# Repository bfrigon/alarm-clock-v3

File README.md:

alarm-clock (V3)
================

Project page [here][link-project]

Specs
-----

- Arduino based design using the ATMEGA2560 MCU.
- Plays MP3/WAV files from a SD card.
- WiFi connectivity (802.11 b/g/n)
- Automatic clock synchronization using NTP
- Send alarm state to Home Assistant via MQTT
- Large RGB seven segment display
- 16x2 character LCD display
- Night lamp
- Touch keypad
- 24h battery backup

---------------------------------------------------

Home Assistant
--------------
The clock can send the alarm switch state and next alarm timestamp to Home Assistant via MQTT. This allows to run home automations based on the alarm time. It also sends other data such as WiFi signal strength, power state, battery voltage and remaining capacity.

[link-project]:https://www.frigon.info/posts/projects/alarm-clock-v3/

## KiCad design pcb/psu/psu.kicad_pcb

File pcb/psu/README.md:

### Bill of material ###

```
Date    : None
Doc. ID : CLKV3-SCH-07
Project : Alarm Clock (V3)
Title   : Power Supply

Part #  : CLKV3-PC-07
REV.    : A

Components : 40
```

------------------------------------------------------------------------------------------------------------------------

| Qty | Ref.             | Description                                      | Value    | Part #           | Footprint               |
|-----|------------------|--------------------------------------------------|----------|------------------|-------------------------|
| 1   | J3               | Header - Single Row - 2 Pos                      | BATTERY  | S2B-PH-K-S       | conn-jst:S2B-PH-K       |
| 1   | J1               | Header - Dual Row - 6 Pos                        | VIN      | TSW-103-07-F-D   | conn-header:HDR-M-2x03  |
| 1   | J2               | Header - Single Row - 4 Pos                      | SIGNAL   | TSW-104-07-F-S   | conn-header:HDR-M-1x04  |
| 2   | Q1-Q2            | 40V NPN small signal transistor                  | MMST3904 | -                | smt-sot:SOT23           |
| 1   | U2               | Li-Ion Battery charger and Power-Path management | -        | BQ24075          | smt-qfn:QFN16-EP-3x3    |
| 1   | U1               | System-side Impedance Track Fuel Gauge           | -        | BQ27441-G1       | smt-son:PDSO-N12        |
| 1   | U3               | 2V to 16V Buck-Boost converter                   | -        | TPS630701        | smt-qfn:VQFN15N         |
| 1   | R2               | Resistor                                         | 0.01 1%  | -                | smt:R-1206              |
| 1   | R10              | Resistor                                         | 0        | -                | smt:R-0603              |
| 1   | R9               | Resistor                                         | 1.1k     | -                | smt:R-0603              |
| 5   | R3-R6, R12       | Resistor                                         | 100k     | -                | smt:R-0603              |
| 1   | C4               | Capacitor                                        | 100nF    | -                | smt:C-0603              |
| 6   | R1, R11, R13-R16 | Resistor                                         | 10k      | -                | smt:R-0603              |
| 2   | C3, C5           | Capacitor                                        | 10uF     | -                | smt:C-0603              |
| 5   | C1-C2, C11-C13   | Capacitor                                        | 10uF     | -                | smt:C-0805              |
| 1   | C10              | Capacitor                                        | 1uF      | -                | smt:C-0603              |
| 3   | C6-C8            | Capacitor                                        | 22uF     | -                | smt:C-0805              |
| 1   | C9               | Capacitor                                        | 470nF    | -                | smt:C-0603              |
| 1   | R8               | Resistor                                         | 5.6k     | -                | smt:R-0603              |
| 1   | R17              | Resistor                                         | 680      | -                | smt:R-0603              |
| 1   | R7               | Resistor                                         | 787k     | -                | smt:R-0603              |
| 1   | D1               | Led                                              | RED      | 150080RS75000    | smt:LED-0805            |
| 1   | L1               | Inductor                                         | 1.5uH    | SPM5030T-1R5M-HZ | smt-inductor:SPM5030-HZ |

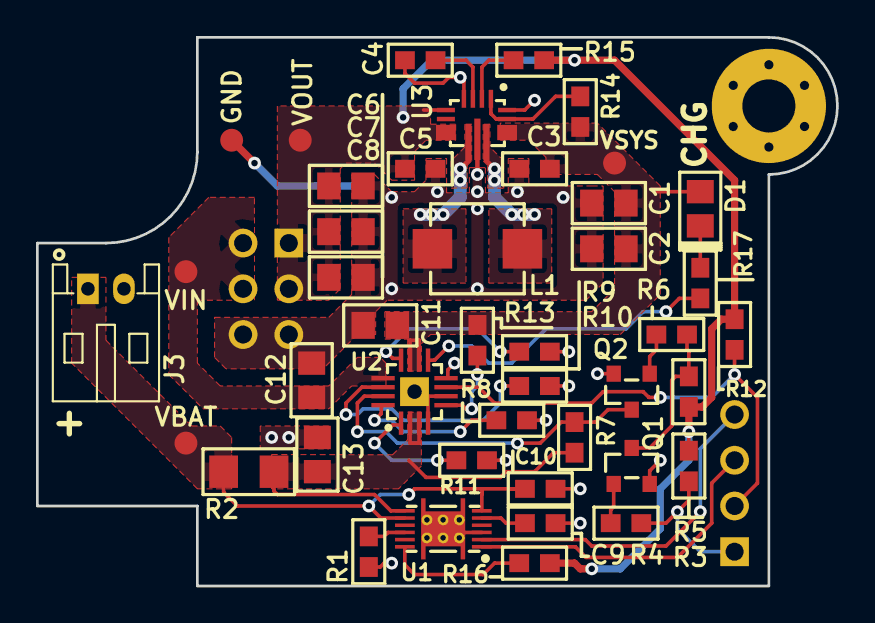
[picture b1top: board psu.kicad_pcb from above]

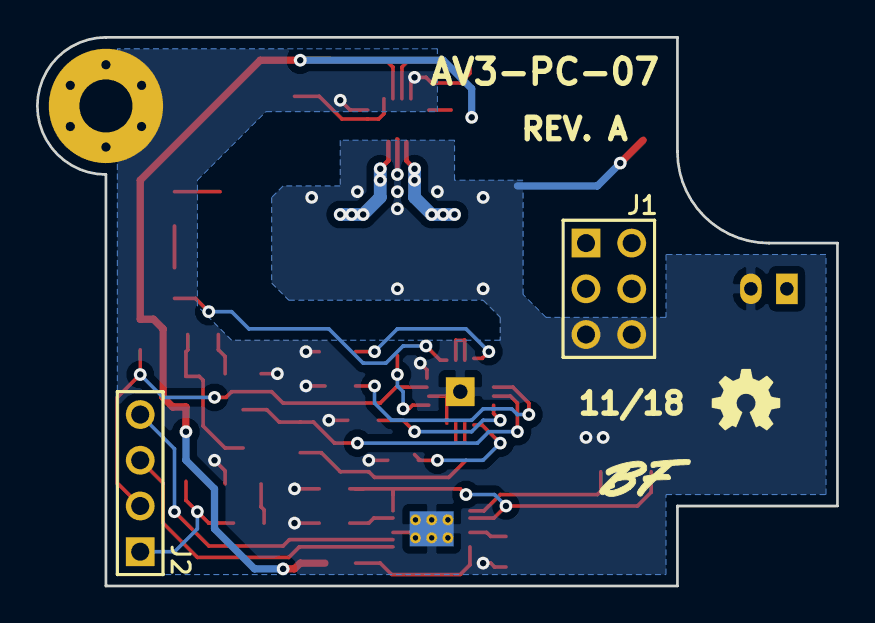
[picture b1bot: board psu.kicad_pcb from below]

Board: 2 copper layers, 44.4 x 30.5 mm, 46 parts (2 on the bottom side), 29 nets.

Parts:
C1, C2, C11, C12, C13: 10uF; C-0805
C3, C5: 10uF; C-0603
C4: 100nF; C-0603
C6, C7, C8: 22uF; C-0805
C9: 470nF; C-0603
C10: 1uF; C-0603
D1: LED; LED-0805
H1: Hole; Hole-Screw-#4
J1: VIN; HDR-M-2x03
J2: SIGNAL; HDR-M-1x04
J3: BATTERY; S2B-PH-K
L1: 1.5uH; SPM5030-HZ
Q1, Q2: MMST3904; SOT23
R1, R11, R13, R14, R15, R16: 10k; R-0603
R2: 0.01 1%; R-1206
R3, R4, R5, R6, R12: 100k; R-0603
R7: 787k; R-0603
R8: 5.6k; R-0603
R9: 1.1k; R-0603
R10: 0; R-0603
R17: 680; R-0603
TP1: VBAT; TEST-POINT-50
TP2: VIN; TEST-POINT-50
TP3: VSYS; TEST-POINT-50
TP4: GND; TEST-POINT-50
TP5: VOUT; TEST-POINT-50
U1: BQ27441-G1; PDSO-N12
U2: BQ24075; QFN16-EP-3x3
U3: TPS630701; VQFN15N

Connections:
+5V: C5.2, C6.2, C7.2, C8.2, J1.1, J1.3, R3.1, R5.1, R12.2, R15.2, R16.2, TP5.1, U3.5, U3.7, U3.8
+BATT: C13.2, R2.2, R7.1, U1.7, U2.2, U2.3
+SYS: C1.2, C2.2, C3.2, C11.2, D1.A, R13.2, R14.2, TP3.1, U2.10, U2.11, U3.12, U3.13
+VIN: C12.2, J1.2, J1.4, TP2.1, U2.13
/BATT_IN: C10.2, J3.1, R2.1, TP1.1, U1.6, U1.8
/L1: L1.1, U3.11
/L2: L1.2, U3.9
/ON_BATT: J2.2, R12.1, U2.7
/SCL: J2.4, U1.2
/SDA: J2.3, U1.1
/SYSOFF: J2.1, R3.2, R4.1
/~CHG: R17.2, U2.9
GND: C1.1, C2.1, C3.1, C4.1, C5.1, C6.1, C7.1, C8.1, C9.2, C10.1, C11.1, C12.1, C13.1, H1.P, J1.5, J1.6, J3.2, Q1.2, Q2.2, R1.2, R8.1, R9.1, R10.1, R11.1, TP4.1, U1.3, U1.EP, U2.4, U2.6, U2.8, U2.EP, U3.4, U3.10, U3.15
unnamed: C4.2, U3.3
unnamed: C9.1, U1.5
unnamed: D1.K, R17.1
unnamed: Q1.1, R4.2
unnamed: Q1.3, R5.2, R6.1
unnamed: Q2.1, R6.2
unnamed: Q2.3, R7.2, U2.15
unnamed: R1.1, U1.10
unnamed: R8.2, U2.16
unnamed: R9.2, U2.12
unnamed: R10.2, U2.14
unnamed: R11.2, U2.1
unnamed: R13.1, U2.5
unnamed: R14.1, U3.1, U3.14
unnamed: R15.1, U3.2
unnamed: R16.1, U1.12

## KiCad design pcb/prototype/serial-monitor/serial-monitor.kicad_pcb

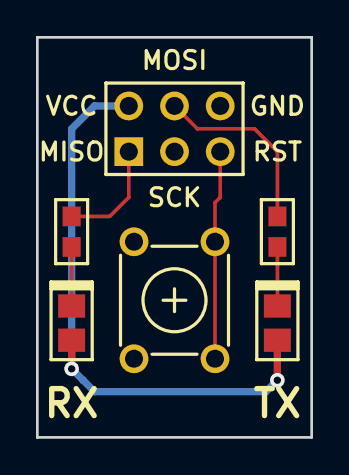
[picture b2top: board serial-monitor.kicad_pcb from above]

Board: 2 copper layers, 15.2 x 22.2 mm, 6 parts (0 on the bottom side), 7 nets.

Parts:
D1, D2: LED; LED-0805
J1: ICSP; HDR-M-2x03
R1, R2: 680; R-0603
SW1: MOM-SPST; B3F-10XX

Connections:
+5V: D1.A, D2.A, J1.2
GND: J1.6, SW1.1
unnamed: D1.K, R1.1
unnamed: D2.K, R2.1
unnamed: J1.1, R1.2
unnamed: J1.4, R2.2
unnamed: J1.5, SW1.2

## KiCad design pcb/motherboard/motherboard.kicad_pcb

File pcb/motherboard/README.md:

### Bill of material ###

```
Date    : 2018-10-29
Doc. ID : CLKV3-SCH-05
Project : Alarm Clock (V3)
Title   : Motherboard

Part #  : CLKV3-PC-05
REV.    : B

Components : 76
```

------------------------------------------------------------------------------------------------------------------------

| Qty | Ref.                            | Description                          | Value      | Part #             | Footprint                       |
|-----|---------------------------------|--------------------------------------|------------|--------------------|---------------------------------|
| 1   | J5                              | Micro SD card connector              | Micro_SD   | 475710001          | conn-io:MOLEX-MICROSD-475710001 |
| 1   | J10                             | Header - Dual Row - 6 Pos            | PSU        | BCS-103-L-D-TE     | conn-header:HDR-M-2x03          |
| 1   | J6                              | Header - Single Row - 4 Pos          | PSU-SIG    | BCS-104-L-S-TE     | conn-header:HDR-M-1x04          |
| 2   | J4, J7                          | Header - Dual Row - 6 Pos            | ICSP       | CES-103-01-T-D     | conn-header:HDR-M-2x03          |
| 1   | J12                             | Header - Single Row - 2 Pos          | DB-C       | DW-02-07-T-S-200   | conn-header:HDR-M-1x02          |
| 1   | J3                              | Header - Single Row - 4 Pos          | DB-B       | DW-04-07-TM-S-200  | conn-header:HDR-M-1x04          |
| 1   | J9                              | Header - Dual Row - 16 Pos           | DB-A       | DW-08-07-T-D-200   | conn-header:HDR-M-2x08          |
| 1   | J1                              | DC Barrel Jack                       | -          | PJ1-021-SMT-TR     | conn-power:CUI-P1J-021-SMT      |
| 1   | J2                              | USB Connector - Type B               | USB-MINI-B | UX60SC-MB-5ST      | conn-io:USB-MB_UX60SC-MB-5ST    |
| 1   | Q1                              | 40V NPN small signal transistor      | MMST3904   | -                  | smt-sot:SOT23                   |
| 1   | U6                              | 600mA CMOS LDO Regulator with enable | -          | AP2112K-3.3        | smt-sot:SOT23-5                 |
| 1   | U3                              | 8-bit Atmel Microcontroller          | -          | ATMEGA16U2-AU      | smt-qfp:QFP-7-32                |
| 1   | U1                              | 8-bit Atmel Microcontroller          | -          | ATMEGA2560-16AU    | smt-qfp:QFP-14-100              |
| 1   | U4                              | IEEE 802.11 b/g/n IoT Module         | -          | ATWINC1500-MR210PB | misc:ATWINC1500-MR              |
| 2   | U5, U7                          | Hex Buffer non-inverting             | -          | CD74HC4050PWR      | smt-sop:TSSOP16                 |
| 1   | U2                              | I2C Real-Time Clock                  | -          | DS3231MZ           | smt-soic:SOIC8                  |
| 8   | R10, R12-R18                    | Resistor                             | 100k       | -                  | smt:R-0603                      |
| 12  | C3, C5-C6, C9-C11, C14, C22-C26 | Capacitor                            | 100nF      | -                  | smt:C-0603                      |
| 9   | R1-R2, R5-R6, R9, R11, R20-R22  | Resistor                             | 10k        | -                  | smt:R-0603                      |
| 1   | C15                             | Capacitor                            | 10nF       | -                  | smt:C-0603                      |
| 4   | C16-C18, C21                    | Capacitor                            | 10uF       | -                  | smt:C-0805                      |
| 3   | R19, R23-R24                    | Resistor                             | 1k         | -                  | smt:R-0603                      |
| 2   | R7-R8                           | Resistor                             | 1M         | -                  | smt:R-0603                      |
| 1   | C13                             | Capacitor                            | 1uF        | -                  | smt:C-0603                      |
| 3   | C4, C19-C20                     | Capacitor                            | 1uF        | -                  | smt:C-0805                      |
| 4   | C1-C2, C7-C8                    | Capacitor                            | 20pF       | -                  | smt:C-0603                      |
| 1   | C12                             | Capacitor                            | 22pF       | -                  | smt:C-0603                      |
| 2   | R3-R4                           | Resistor                             | 22         | -                  | smt:R-0603                      |
| 1   | F1                              | Resistor                             | 500mA      | -                  | smt:R-1206                      |
| 1   | DA1                             | TVS Diode Array                      | SR05       | -                  | smt-sot:SOT-143                 |
| 2   | D1-D2                           | Diode                                | -          | CD1206-S01575      | smt:D-1206                      |
| 2   | Y1-Y2                           | Crystal                              | 16.00 MHz  | ECS-160-20-3X-TR   | crystals:smt-CSM-3X-7x4mm       |
| 1   | B1                              | Battery - 1 cell                     | CR1220     | S8411-45R          | conn-power:S8411-45R            |
| 1   | SW1                             | Momentary SPST switch                | RESET      | B3F-1000           | switches:B3F-10XX               |

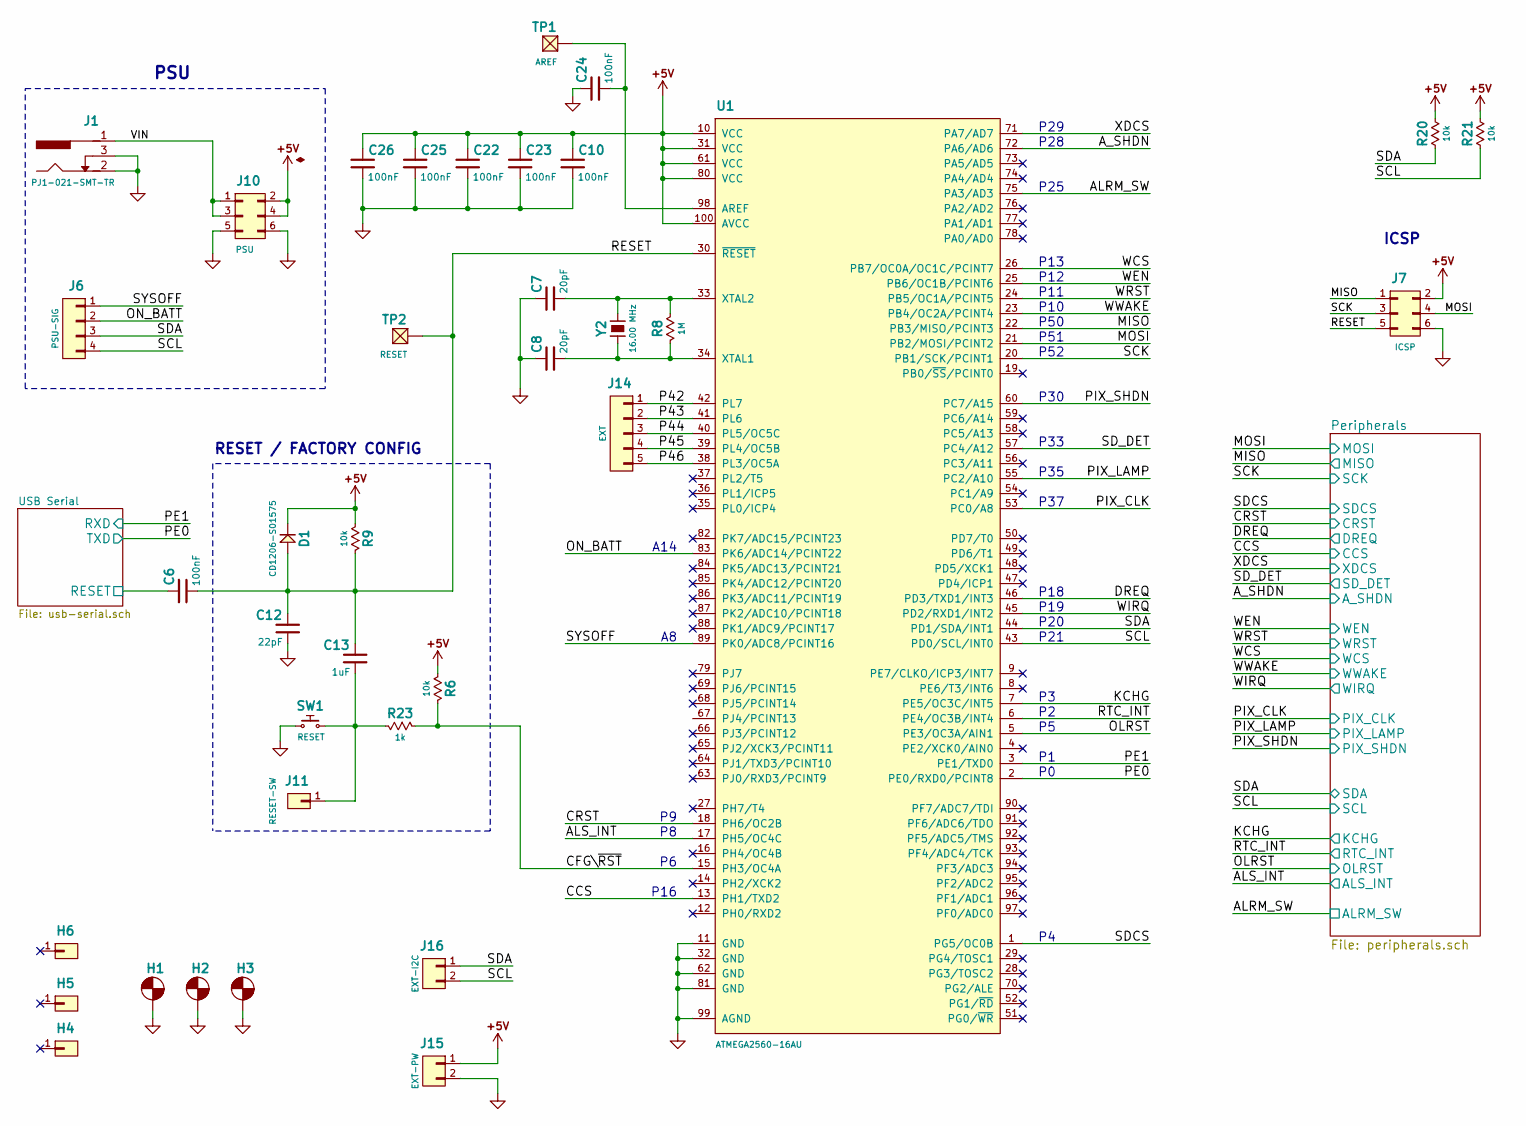
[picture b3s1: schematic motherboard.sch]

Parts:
C6, C10, C22, C23, C24, C25, C26: 100nF; C-0603
C7, C8: 20pF; C-0603
C12: 22pF; C-0603
C13: 1uF; C-0603
D1: CD1206-S01575; D-1206; Part CD1206-S01575
H1, H2, H3: Hole; Hole-Screw-#4
H4, H5: HEADER-1x01; SolderPad-100x500
H6: HEADER-1x01; SolderPad-100x300
J1: -; CUI-P1J-021-SMT; Part PJ1-021-SMT-TR
J6: PSU-SIG; HDR-M-1x04; Part BCS-104-L-S-TE
J7: ICSP; HDR-M-2x03; Part CES-103-01-T-D
J10: PSU; HDR-M-2x03; Part BCS-103-L-D-TE
J11: RESET-SW; WP-50mil-1x01
J14: EXT; WP-40mil-1x05
J15: EXT-PW; WP-50mil-1x02
J16: EXT-I2C; WP-50mil-1x02
R6, R9, R20, R21: 10k; R-0603
R8: 1M; R-0603
R23: 1k; R-0603
SW1: RESET; B3F-10XX; Part B3F-1000
TP1: AREF; TEST-POINT-50
TP2: RESET; TEST-POINT-50
U1: ATMEGA2560-16AU; QFP-14-100
Y2: 16.00 MHz; smt-CSM-3X-7x4mm; Part ECS-160-20-3X-TR

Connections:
/ALRM_SW: U1.75 (PA3/AD3); also elsewhere on the board
/ALS_INT: U1.17 (PH5/OC4C); also elsewhere on the board
/A_SHDN: U1.72 (PA6/AD6); also elsewhere on the board
/CCS: U1.13 (PH1/TXD2); also elsewhere on the board
/CFG\~RST: R6.1, R23.1, U1.15 (PH3/OC4A)
/CRST: U1.18 (PH6/OC2B); also elsewhere on the board
/DREQ: U1.46 (PD3/TXD1/INT3); also elsewhere on the board
/KCHG: U1.7 (PE5/OC3C/INT5); also elsewhere on the board
/MISO: J7.1, U1.22 (PB3/MISO/PCINT3); also elsewhere on the board
/MOSI: J7.4, U1.21 (PB2/MOSI/PCINT2); also elsewhere on the board
/OLRST: U1.5 (PE3/OC3A/AIN1); also elsewhere on the board
/ON_BATT: J6.2, U1.83 (PK6/ADC14/PCINT22)
/P42: J14.1, U1.42 (PL7)
/P43: J14.2, U1.41 (PL6)
/P44: J14.3, U1.40 (PL5/OC5C)
/P45: J14.4, U1.39 (PL4/OC5B)
/P46: J14.5, U1.38 (PL3/OC5A)
/PE0: U1.2 (PE0/RXD0/PCINT8); also elsewhere on the board
/PE1: U1.3 (PE1/TXD0); also elsewhere on the board
/PIX_CLK: U1.53 (PC0/A8); also elsewhere on the board
/PIX_LAMP: U1.55 (PC2/A10); also elsewhere on the board
/PIX_SHDN: U1.60 (PC7/A15); also elsewhere on the board
/RESET: C6.1, C12.2, C13.2, D1.A, J7.5, R9.1, TP2.1, U1.30 (~RESET)
/RTC_INT: U1.6 (PE4/OC3B/INT4); also elsewhere on the board
/SCK: J7.3, U1.20 (PB1/SCK/PCINT1); also elsewhere on the board
/SCL: J6.4, J16.2, R21.1, U1.43 (PD0/SCL/INT0); also elsewhere on the board
/SDA: J6.3, J16.1, R20.1, U1.44 (PD1/SDA/INT1); also elsewhere on the board
/SDCS: U1.1 (PG5/OC0B); also elsewhere on the board
/SD_DET: U1.57 (PC4/A12); also elsewhere on the board
/SYSOFF: J6.1, U1.89 (PK0/ADC8/PCINT16)
/USB Serial/RESET: C6.2; also elsewhere on the board
/VIN: J1.1, J10.1, J10.3
/WCS: U1.26 (PB7/OC0A/OC1C/PCINT7); also elsewhere on the board
/WEN: U1.25 (PB6/OC1B/PCINT6); also elsewhere on the board
/WIRQ: U1.45 (PD2/RXD1/INT2); also elsewhere on the board
/WRST: U1.24 (PB5/OC1A/PCINT5); also elsewhere on the board
/WWAKE: U1.23 (PB4/OC2A/PCINT4); also elsewhere on the board
/XDCS: U1.71 (PA7/AD7); also elsewhere on the board
GND: C7.2, C8.2, C10.1, C12.1, C22.1, C23.1, C24.2, C25.1, C26.1, H1.P, H2.P, H3.P, J1.2, J1.3, J7.6, J10.5, J10.6, J15.2, SW1.2, U1.11 (GND), U1.32 (GND), U1.62 (GND), U1.81 (GND), U1.99 (AGND); also elsewhere on the board
unnamed: C7.1, R8.1, U1.33 (XTAL2), Y2.2
unnamed: C8.1, R8.2, U1.34 (XTAL1), Y2.1
unnamed: C13.1, J11.1, R23.2, SW1.1
unnamed: C24.1, TP1.1, U1.98 (AREF)

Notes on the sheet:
RESET / FACTORY CONFIG
P29
P28
P25
P13
P12
P11
P10
P50
P51
P52
P30
P33
P35
P37
P18
P19
P20
P21
P16
ICSP
A14
PSU

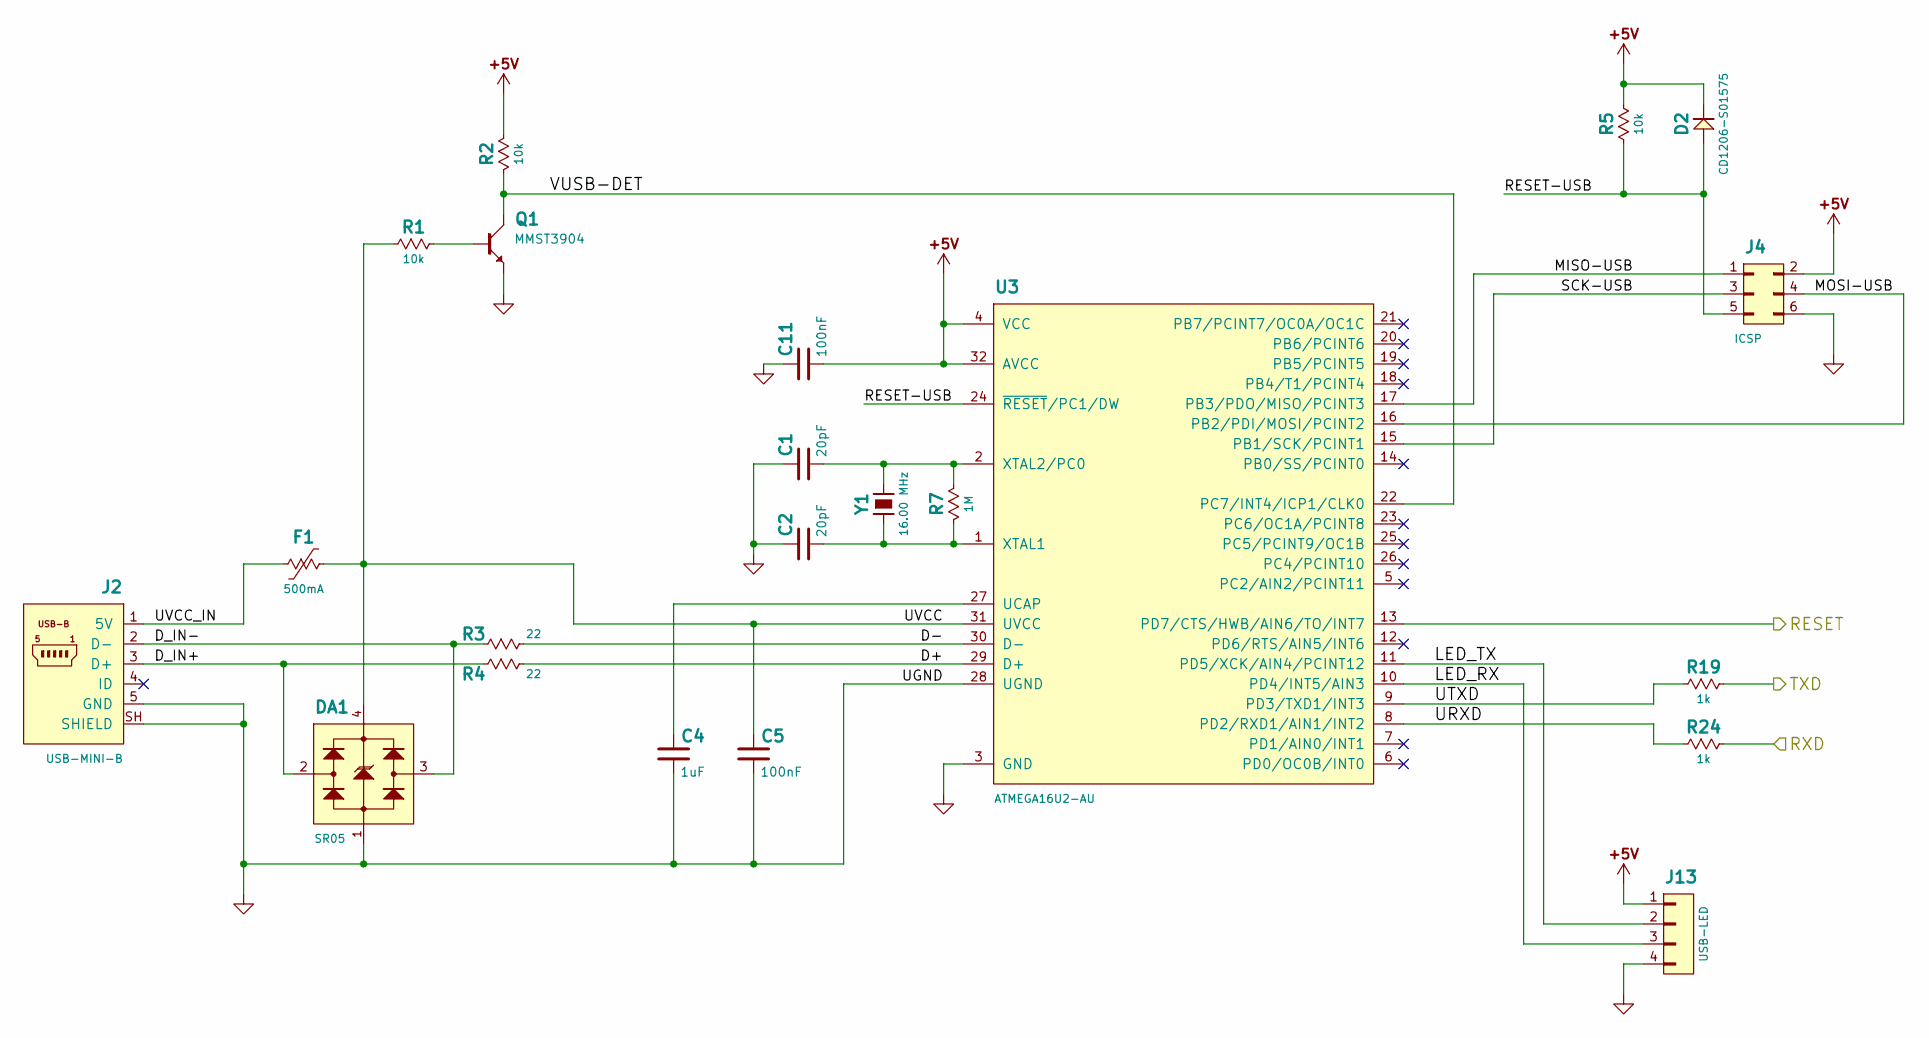
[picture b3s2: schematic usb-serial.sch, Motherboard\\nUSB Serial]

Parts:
C1, C2: 20pF; C-0603
C4: 1uF; C-0805
C5, C11: 100nF; C-0603
D2: CD1206-S01575; D-1206; Part CD1206-S01575
DA1: SR05; SOT-143
F1: 500mA; R-1206
J2: USB-MINI-B; USB-MB_UX60SC-MB-5ST; Part UX60SC-MB-5ST
J4: ICSP; HDR-M-2x03; Part CES-103-01-T-D
J13: USB-LED; WP-50mil-1x04
Q1: MMST3904; SOT23
R1, R2, R5: 10k; R-0603
R3, R4: 22; R-0603
R7: 1M; R-0603
R19, R24: 1k; R-0603
U3: ATMEGA16U2-AU; QFP-7-32
Y1: 16.00 MHz; smt-CSM-3X-7x4mm; Part ECS-160-20-3X-TR

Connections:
/PE0: R19.2; also elsewhere on the board
/PE1: R24.2; also elsewhere on the board
/USB Serial/D+: R4.2, U3.29 (D+)
/USB Serial/D-: R3.2, U3.30 (D-)
/USB Serial/D_IN+: DA1.2, J2.3 (D+), R4.1
/USB Serial/D_IN-: DA1.3, J2.2 (D-), R3.1
/USB Serial/LED_RX: J13.3, U3.10 (PD4/INT5/AIN3)
/USB Serial/LED_TX: J13.2, U3.11 (PD5/XCK/AIN4/PCINT12)
/USB Serial/MISO-USB: J4.1, U3.17 (PB3/PDO/MISO/PCINT3)
/USB Serial/MOSI-USB: J4.4, U3.16 (PB2/PDI/MOSI/PCINT2)
/USB Serial/RESET: U3.13 (PD7/CTS/HWB/AIN6/TO/INT7); also elsewhere on the board
/USB Serial/RESET-USB: D2.A, J4.5, R5.1, U3.24 (~RESET~/PC1/DW)
/USB Serial/SCK-USB: J4.3, U3.15 (PB1/SCK/PCINT1)
/USB Serial/URXD: R24.1, U3.8 (PD2/RXD1/AIN1/INT2)
/USB Serial/UTXD: R19.1, U3.9 (PD3/TXD1/INT3)
/USB Serial/UVCC: C5.2, DA1.4, F1.2, R1.1, U3.31 (UVCC)
/USB Serial/UVCC_IN: F1.1, J2.1 (5V)
/USB Serial/VUSB-DET: Q1.3 (C), R2.2, U3.22 (PC7/INT4/ICP1/CLK0)
GND: C1.2, C2.2, C4.1, C5.1, C11.2, DA1.1, J2.5 (GND), J2.SH (SHIELD), J4.6, J13.4, Q1.2 (E), U3.3 (GND), U3.28 (UGND); also elsewhere on the board
unnamed: C1.1, R7.1, U3.2 (XTAL2/PC0), Y1.2
unnamed: C2.1, R7.2, U3.1 (XTAL1), Y1.1
unnamed: C4.2, U3.27 (UCAP)
unnamed: Q1.1 (B), R1.2

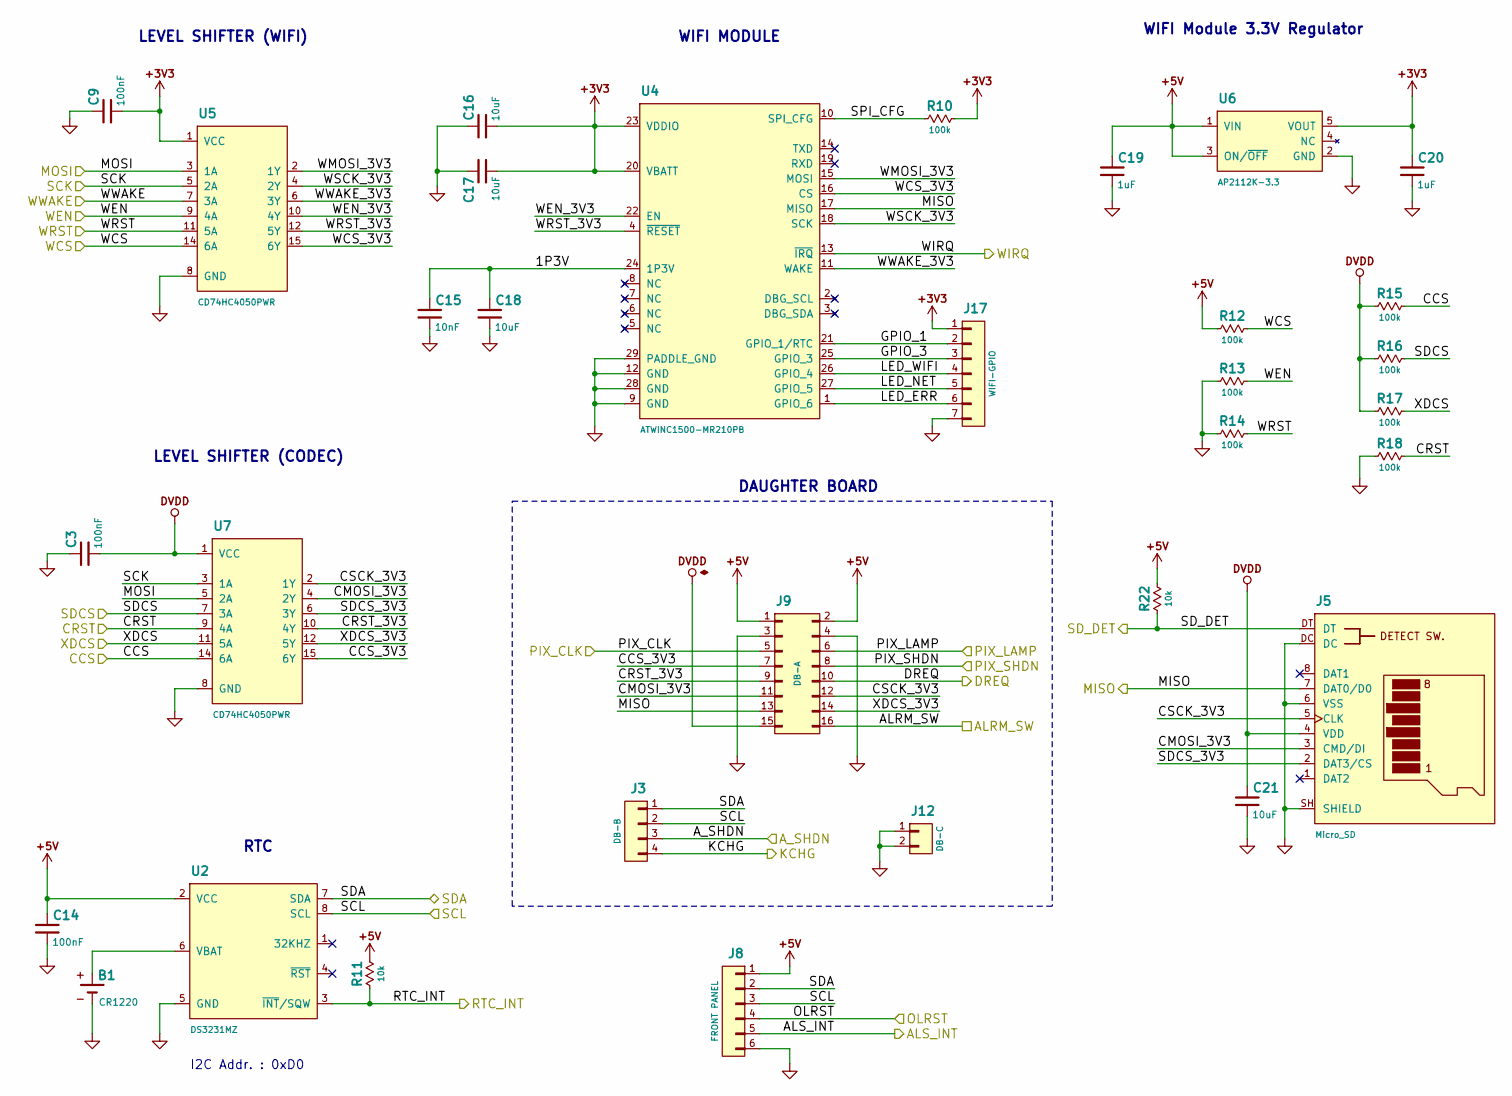
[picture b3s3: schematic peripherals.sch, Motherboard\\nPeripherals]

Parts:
B1: CR1220; S8411-45R; Part S8411-45R
C3, C9, C14: 100nF; C-0603
C15: 10nF; C-0603
C16, C17, C18, C21: 10uF; C-0805
C19, C20: 1uF; C-0805
J3: DB-B; HDR-M-1x04; Part DW-04-07-TM-S-200
J5: Micro_SD; MOLEX-MICROSD-475710001; Part 475710001
J8: FRONT PANEL; WP-EDGE-RL-50mil-1x06
J9: DB-A; HDR-M-2x08; Part DW-08-07-T-D-200
J12: DB-C; HDR-M-1x02; Part DW-02-07-T-S-200
J17: WIFI-GPIO; WP-40mil-1x07
R10, R12, R13, R14, R15, R16, R17, R18: 100k; R-0603
R11, R22: 10k; R-0603
U2: DS3231MZ; SOIC8
U4: ATWINC1500-MR210PB; ATWINC1500-MR
U5, U7: CD74HC4050PWR; TSSOP16
U6: AP2112K-3.3; SOT23-5

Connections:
+3V3: C9.1, C16.1, C17.1, C20.2, J17.1, R10.2, U4.20 (VBATT), U4.23 (VDDIO), U5.1 (VCC), U6.5 (VOUT)
/ALRM_SW: J9.16; also elsewhere on the board
/ALS_INT: J8.5; also elsewhere on the board
/A_SHDN: J3.3; also elsewhere on the board
/CCS: R15.2, U7.14 (6A); also elsewhere on the board
/CRST: R18.2, U7.9 (4A); also elsewhere on the board
/DREQ: J9.10; also elsewhere on the board
/KCHG: J3.4; also elsewhere on the board
/MISO: J5.7 (DAT0/D0), J9.13, U4.17 (MISO); also elsewhere on the board
/MOSI: U5.3 (1A), U7.5 (2A); also elsewhere on the board
/OLRST: J8.4; also elsewhere on the board
/PIX_CLK: J9.5; also elsewhere on the board
/PIX_LAMP: J9.6; also elsewhere on the board
/PIX_SHDN: J9.8; also elsewhere on the board
/Peripherals/1P3V: C15.2, C18.2, U4.24 (1P3V)
/Peripherals/CCS_3V3: J9.7, U7.15 (6Y)
/Peripherals/CMOSI_3V3: J5.3 (CMD/DI), J9.11, U7.4 (2Y)
/Peripherals/CRST_3V3: J9.9, U7.10 (4Y)
/Peripherals/CSCK_3V3: J5.5 (CLK), J9.12, U7.2 (1Y)
/Peripherals/GPIO_1: J17.2, U4.21 (GPIO_1/RTC)
/Peripherals/GPIO_3: J17.3, U4.25 (GPIO_3)
/Peripherals/LED_ERR: J17.6, U4.1 (GPIO_6)
/Peripherals/LED_NET: J17.5, U4.27 (GPIO_5)
/Peripherals/LED_WIFI: J17.4, U4.26 (GPIO_4)
/Peripherals/SDCS_3V3: J5.2 (DAT3/CS), U7.6 (3Y)
/Peripherals/SPI_CFG: R10.1, U4.10 (SPI_CFG)
/Peripherals/WCS_3V3: U4.16 (CS), U5.15 (6Y)
/Peripherals/WEN_3V3: U4.22 (EN), U5.10 (4Y)
/Peripherals/WMOSI_3V3: U4.15 (MOSI), U5.2 (1Y)
/Peripherals/WRST_3V3: U4.4 (~RESET), U5.12 (5Y)
/Peripherals/WSCK_3V3: U4.18 (SCK), U5.4 (2Y)
/Peripherals/WWAKE_3V3: U4.11 (WAKE), U5.6 (3Y)
/Peripherals/XDCS_3V3: J9.14, U7.12 (5Y)
/RTC_INT: R11.1, U2.3 (~INT~/SQW); also elsewhere on the board
/SCK: U5.5 (2A), U7.3 (1A); also elsewhere on the board
/SCL: J3.2, J8.3, U2.8 (SCL); also elsewhere on the board
/SDA: J3.1, J8.2, U2.7 (SDA); also elsewhere on the board
/SDCS: R16.2, U7.7 (3A); also elsewhere on the board
/SD_DET: J5.DT, R22.1; also elsewhere on the board
/WCS: R12.2, U5.14 (6A); also elsewhere on the board
/WEN: R13.2, U5.9 (4A); also elsewhere on the board
/WIRQ: U4.13 (~IRQ); also elsewhere on the board
/WRST: R14.2, U5.11 (5A); also elsewhere on the board
/WWAKE: U5.7 (3A); also elsewhere on the board
/XDCS: R17.2, U7.11 (5A); also elsewhere on the board
GND: B1.N, C3.2, C9.2, C14.1, C15.1, C16.2, C17.2, C18.1, C19.1, C20.1, C21.1, J5.6 (VSS), J5.DC, J5.SH (SHIELD), J8.6, J9.3, J9.4, J12.1, J12.2, J17.7, R13.1, R14.1, R18.1, U2.5 (GND), U4.9 (GND), U4.12 (GND), U4.28 (GND), U4.29 (PADDLE_GND), U5.8 (GND), U6.2 (GND), U7.8 (GND); also elsewhere on the board
unnamed: B1.P, U2.6 (VBAT)

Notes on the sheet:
WIFI MODULE
RTC
DAUGHTER BOARD
LEVEL SHIFTER (WIFI)
LEVEL SHIFTER (CODEC)
WIFI Module 3.3V Regulator
I2C Addr. : 0xD0

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
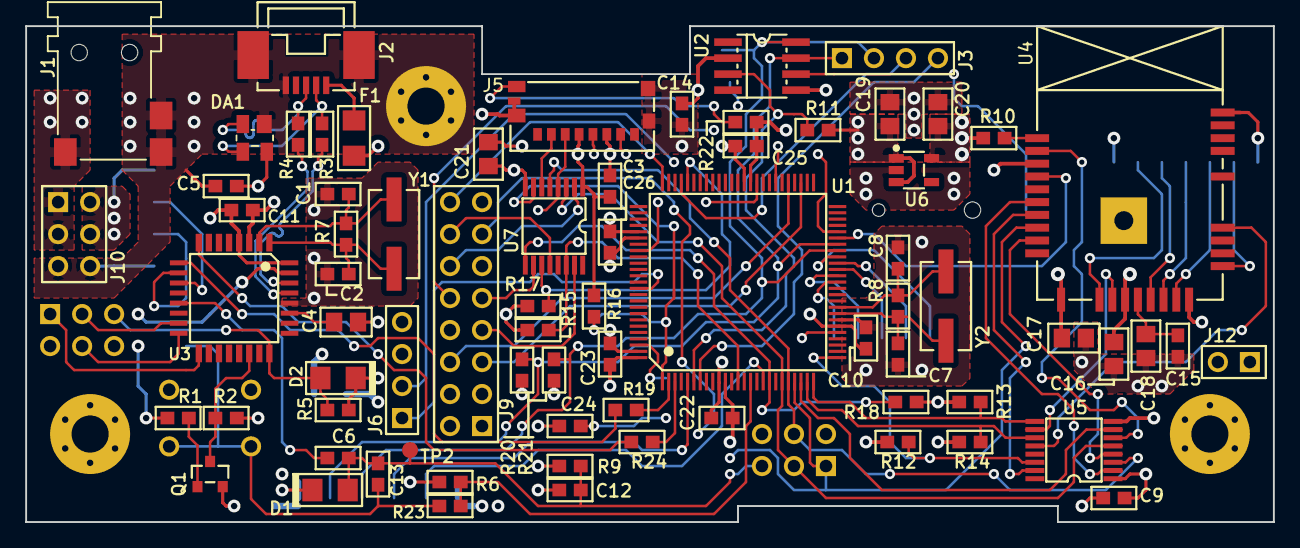
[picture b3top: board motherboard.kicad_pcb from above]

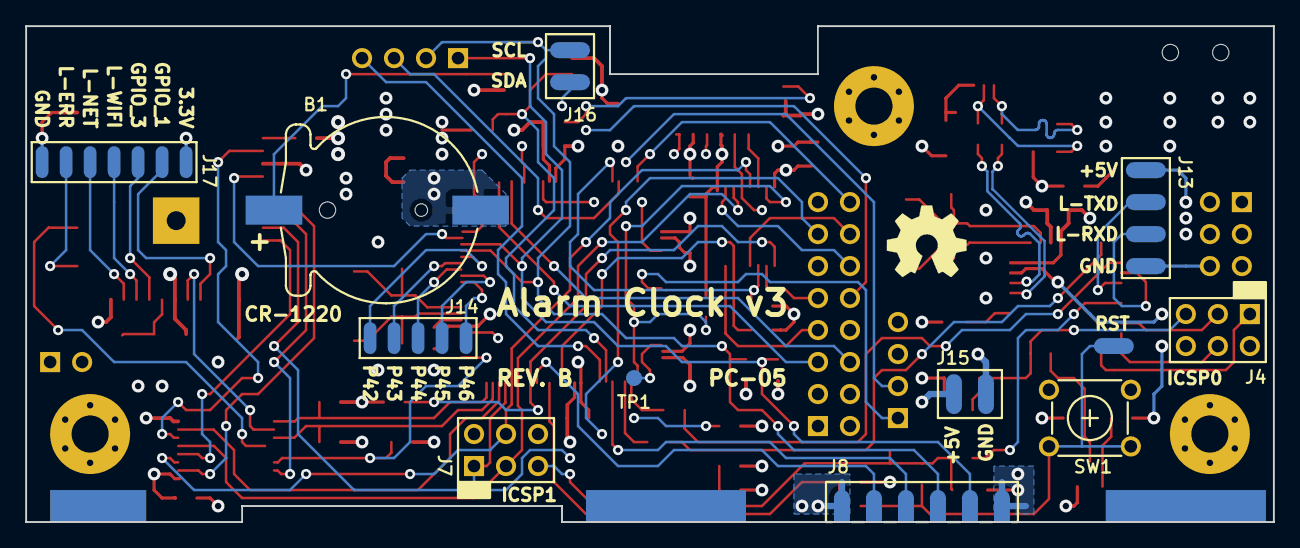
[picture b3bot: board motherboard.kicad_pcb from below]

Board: 4 copper layers, 99.1 x 39.4 mm, 91 parts (15 on the bottom side), 85 nets.
